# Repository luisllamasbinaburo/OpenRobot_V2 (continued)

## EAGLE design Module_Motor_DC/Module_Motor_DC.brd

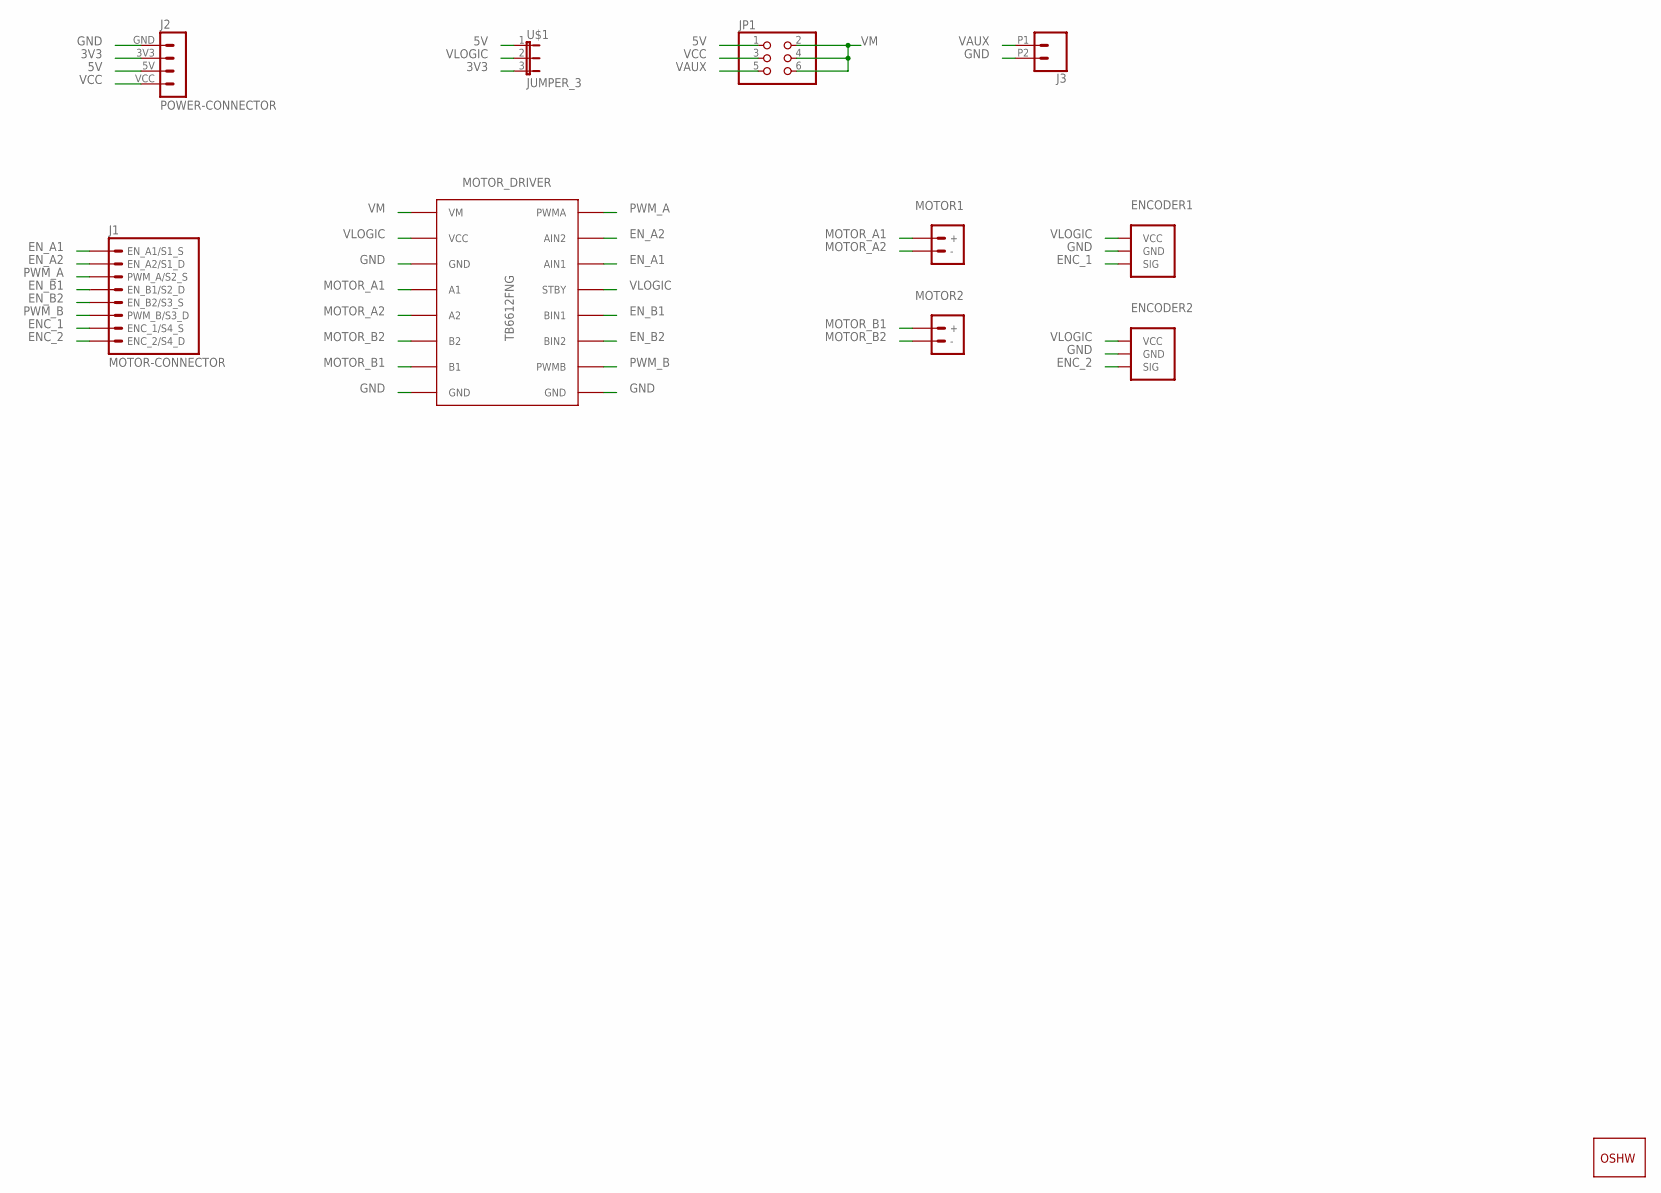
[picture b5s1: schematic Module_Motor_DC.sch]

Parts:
ENCODER1, ENCODER2: ENCODER/OCT; ENCODER
GOLD_ORB_SM1: OSHWLOGO_GOLD_ORB_MED; OSHW1
J1: MOTOR-CONNECTOR
J2: POWER-CONNECTOR
J3: CONN_022.54MM_SCREWTERM; 1X02_2.54_SCREWTERM
JP1: JUMPER_3X2/OCT; JUMPER_3X2
MOTOR1, MOTOR2: MOTOR-TERMINAL5MM; SCREWTERMINAL-5MM-2
MOTOR_DRIVER: TB6612FNG
U$1: JUMPER_3

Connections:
3V3: J2.3V3, U$1.3
5V: J2.5V, JP1.1, U$1.1
ENC_1: ENCODER1.SIG, J1.ENC_1/S4_S
ENC_2: ENCODER2.SIG, J1.ENC_2/S4_D
EN_A1: J1.EN_A1/S1_S, MOTOR_DRIVER.AIN1
EN_A2: J1.EN_A2/S1_D, MOTOR_DRIVER.AIN2
EN_B1: J1.EN_B1/S2_D, MOTOR_DRIVER.BIN1
EN_B2: J1.EN_B2/S3_S, MOTOR_DRIVER.BIN2
GND: ENCODER1.GND, ENCODER2.GND, J2.GND, J3.P2 (2), MOTOR_DRIVER.GND1 (GND), MOTOR_DRIVER.GND2 (GND), MOTOR_DRIVER.GND3 (GND)
MOTOR_A1: MOTOR1.+, MOTOR_DRIVER.A1
MOTOR_A2: MOTOR1.-, MOTOR_DRIVER.A2
MOTOR_B1: MOTOR2.+, MOTOR_DRIVER.B1
MOTOR_B2: MOTOR2.-, MOTOR_DRIVER.B2
PWM_A: J1.PWM_A/S2_S, MOTOR_DRIVER.PWMA
PWM_B: J1.PWM_B/S3_D, MOTOR_DRIVER.PWMB
VAUX: J3.P1 (1), JP1.5
VCC: J2.VCC, JP1.3
VLOGIC: ENCODER1.VCC, ENCODER2.VCC, MOTOR_DRIVER.STBY, MOTOR_DRIVER.VCC, U$1.2
VM: JP1.2, JP1.4, JP1.6, MOTOR_DRIVER.VM

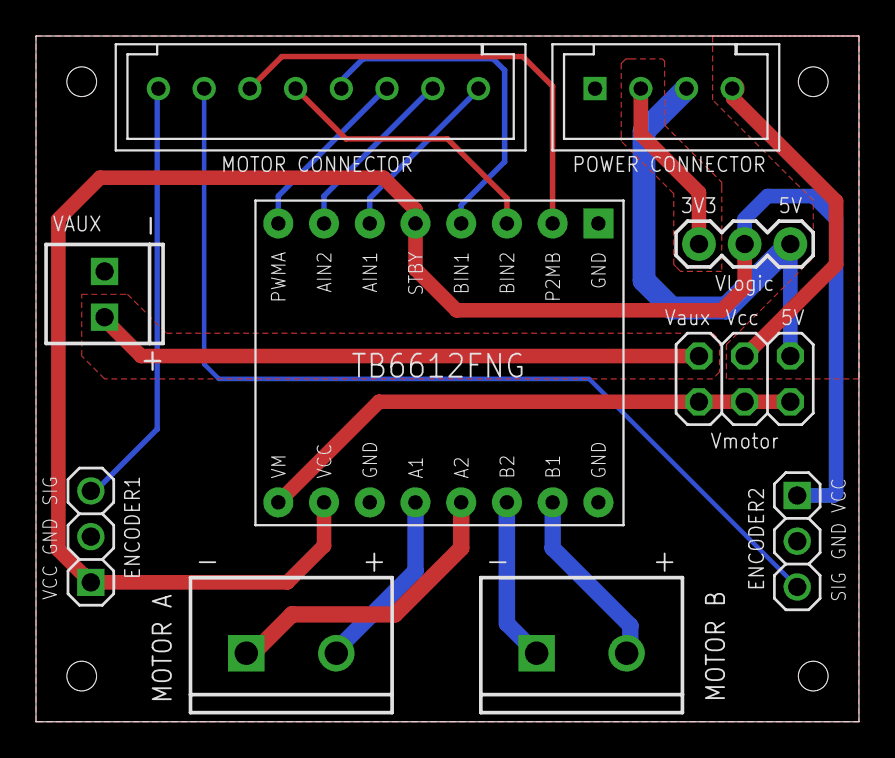
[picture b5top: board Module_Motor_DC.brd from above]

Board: 2 copper layers, 45.7 x 38.1 mm, 11 parts (1 on the bottom side), 19 nets.

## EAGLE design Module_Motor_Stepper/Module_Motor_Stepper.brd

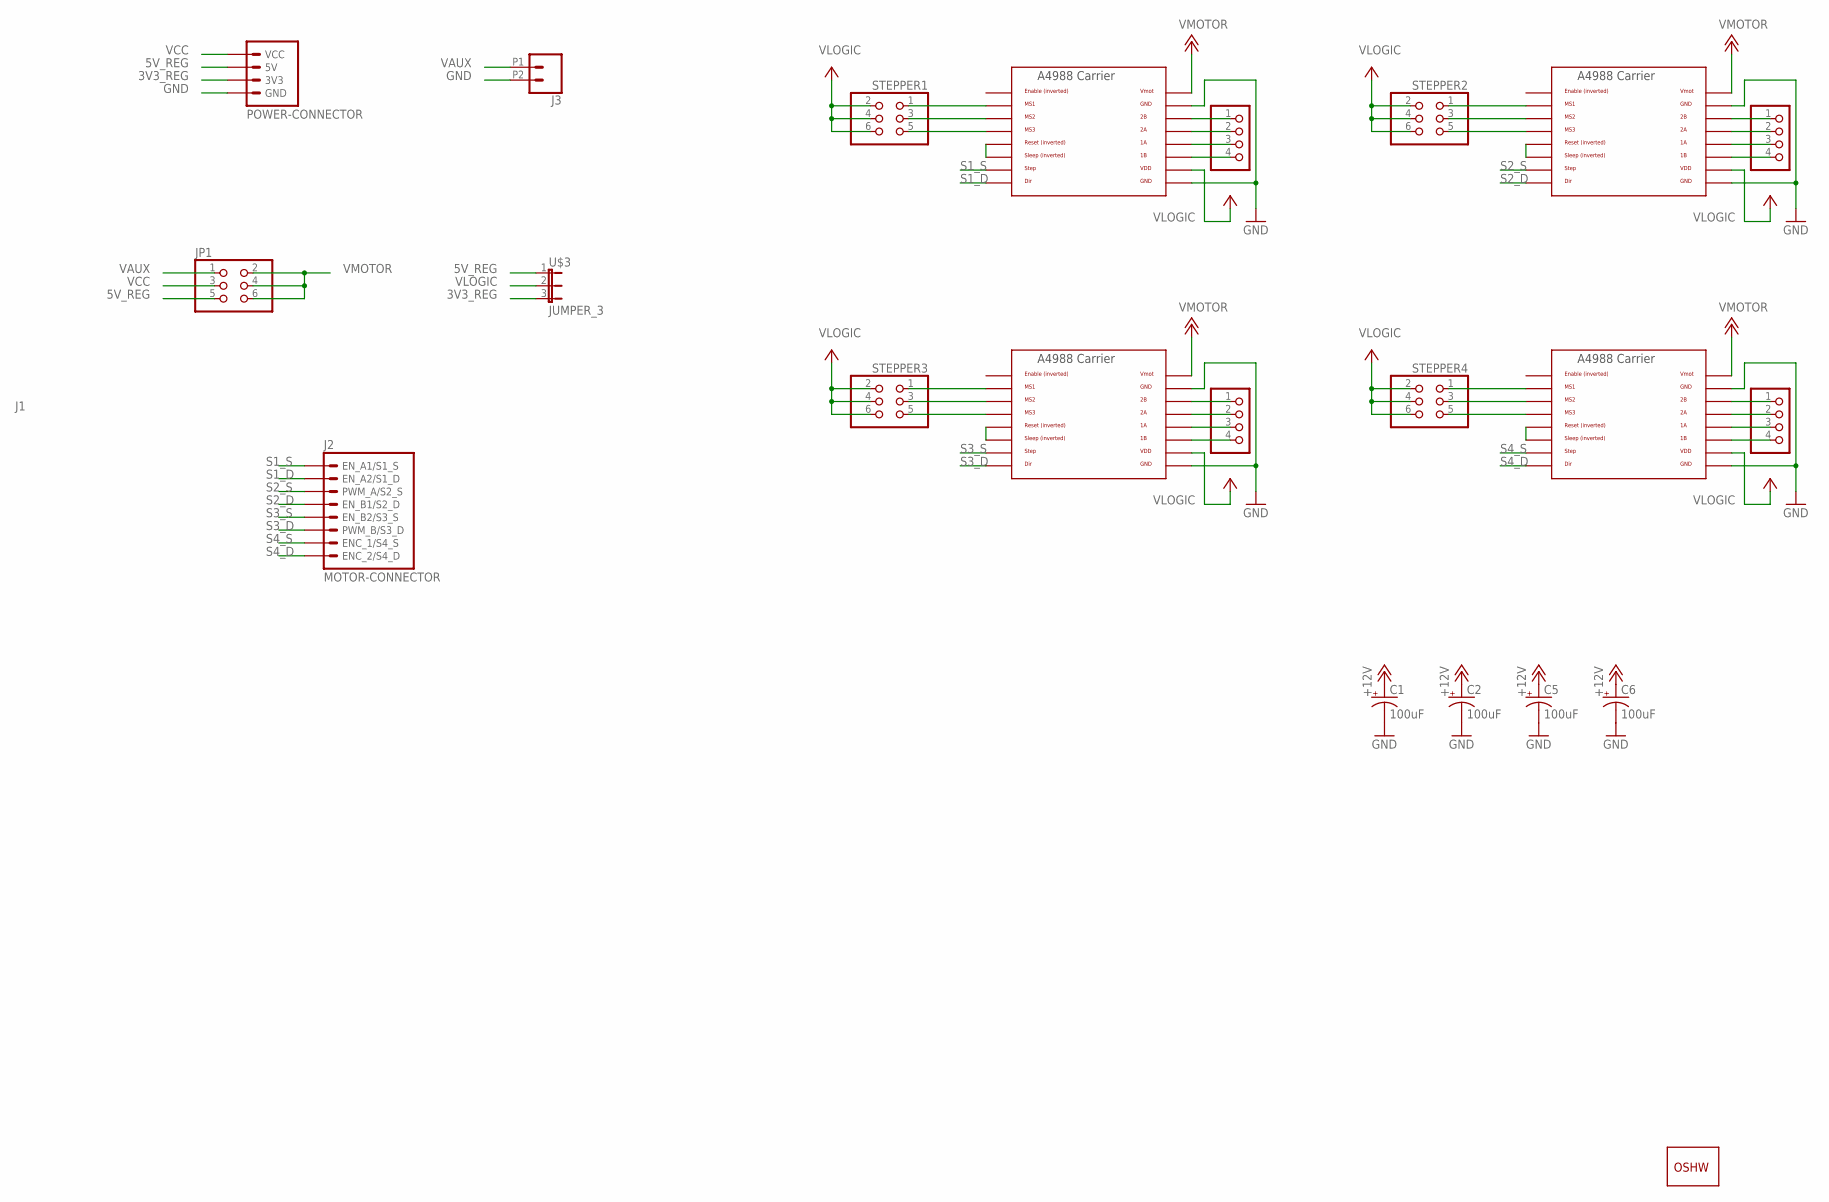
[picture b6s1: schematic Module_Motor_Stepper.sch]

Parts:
C1, C2, C5, C6: 100uF; 153CLV-0605
E0-MOT1, E0-MOT2, E0-MOT4, E0-MOT6: PINHD-1X4; 1X04
GOLD_ORB_SM1: OSHWLOGO_GOLD_ORB_MED; OSHW1
J1: POWER-CONNECTOR
J2: MOTOR-CONNECTOR
J3: CONN_022.54MM_SCREWTERM; 1X02_2.54_SCREWTERM
JP1: JUMPER_3X2/OCT; JUMPER_3X2
STEPPER1, STEPPER2, STEPPER3, STEPPER4: PINHD-2X3; 2X03
U$1, U$2, U$5, U$7: A4988BREAKOUT
U$3: JUMPER_3

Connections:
3V3_REG: J1.3V3, U$3.3
5V_REG: J1.5V, JP1.5, U$3.1
GND: C1.-, C2.-, C5.-, C6.-, J1.GND, J3.P2 (2), U$1.GND, U$1.GND@0 (GND), U$2.GND, U$2.GND@0 (GND), U$5.GND, U$5.GND@0 (GND), U$7.GND, U$7.GND@0 (GND)
unnamed: STEPPER1.5, U$1.MS3
unnamed: U$1.RST, U$1.SLP (SLEEP)
unnamed: STEPPER1.1, U$1.MS1
unnamed: STEPPER1.3, U$1.MS2
unnamed: E0-MOT1.1, U$1.2B
unnamed: E0-MOT1.2, U$1.2A
unnamed: E0-MOT1.3, U$1.1A
unnamed: E0-MOT1.4, U$1.1B
unnamed: STEPPER2.5, U$2.MS3
unnamed: U$2.RST, U$2.SLP (SLEEP)
unnamed: STEPPER2.1, U$2.MS1
unnamed: STEPPER2.3, U$2.MS2
unnamed: E0-MOT2.1, U$2.2B
unnamed: E0-MOT2.2, U$2.2A
unnamed: E0-MOT2.3, U$2.1A
unnamed: E0-MOT2.4, U$2.1B
unnamed: STEPPER3.5, U$5.MS3
unnamed: U$5.RST, U$5.SLP (SLEEP)
unnamed: STEPPER3.1, U$5.MS1
unnamed: STEPPER3.3, U$5.MS2
unnamed: E0-MOT4.1, U$5.2B
unnamed: E0-MOT4.2, U$5.2A
unnamed: E0-MOT4.3, U$5.1A
unnamed: E0-MOT4.4, U$5.1B
unnamed: STEPPER4.5, U$7.MS3
unnamed: U$7.RST, U$7.SLP (SLEEP)
unnamed: STEPPER4.1, U$7.MS1
unnamed: STEPPER4.3, U$7.MS2
unnamed: E0-MOT6.1, U$7.2B
unnamed: E0-MOT6.2, U$7.2A
unnamed: E0-MOT6.3, U$7.1A
unnamed: E0-MOT6.4, U$7.1B
S1_D: J2.EN_A2/S1_D, U$1.DIR
S1_S: J2.EN_A1/S1_S, U$1.STEP
S2_D: J2.EN_B1/S2_D, U$2.DIR
S2_S: J2.PWM_A/S2_S, U$2.STEP
S3_D: J2.PWM_B/S3_D, U$5.DIR
S3_S: J2.EN_B2/S3_S, U$5.STEP
S4_D: J2.ENC_2/S4_D, U$7.DIR
S4_S: J2.ENC_1/S4_S, U$7.STEP
VAUX: J3.P1 (1), JP1.1
VCC: J1.VCC, JP1.3
VLOGIC: STEPPER1.2, STEPPER1.4, STEPPER1.6, STEPPER2.2, STEPPER2.4, STEPPER2.6, STEPPER3.2, STEPPER3.4, STEPPER3.6, STEPPER4.2, STEPPER4.4, STEPPER4.6, U$1.VDD, U$2.VDD, U$3.2, U$5.VDD, U$7.VDD
VMOTOR: C1.+, C2.+, C5.+, C6.+, JP1.2, JP1.4, JP1.6, U$1.VMOT, U$2.VMOT, U$5.VMOT, U$7.VMOT

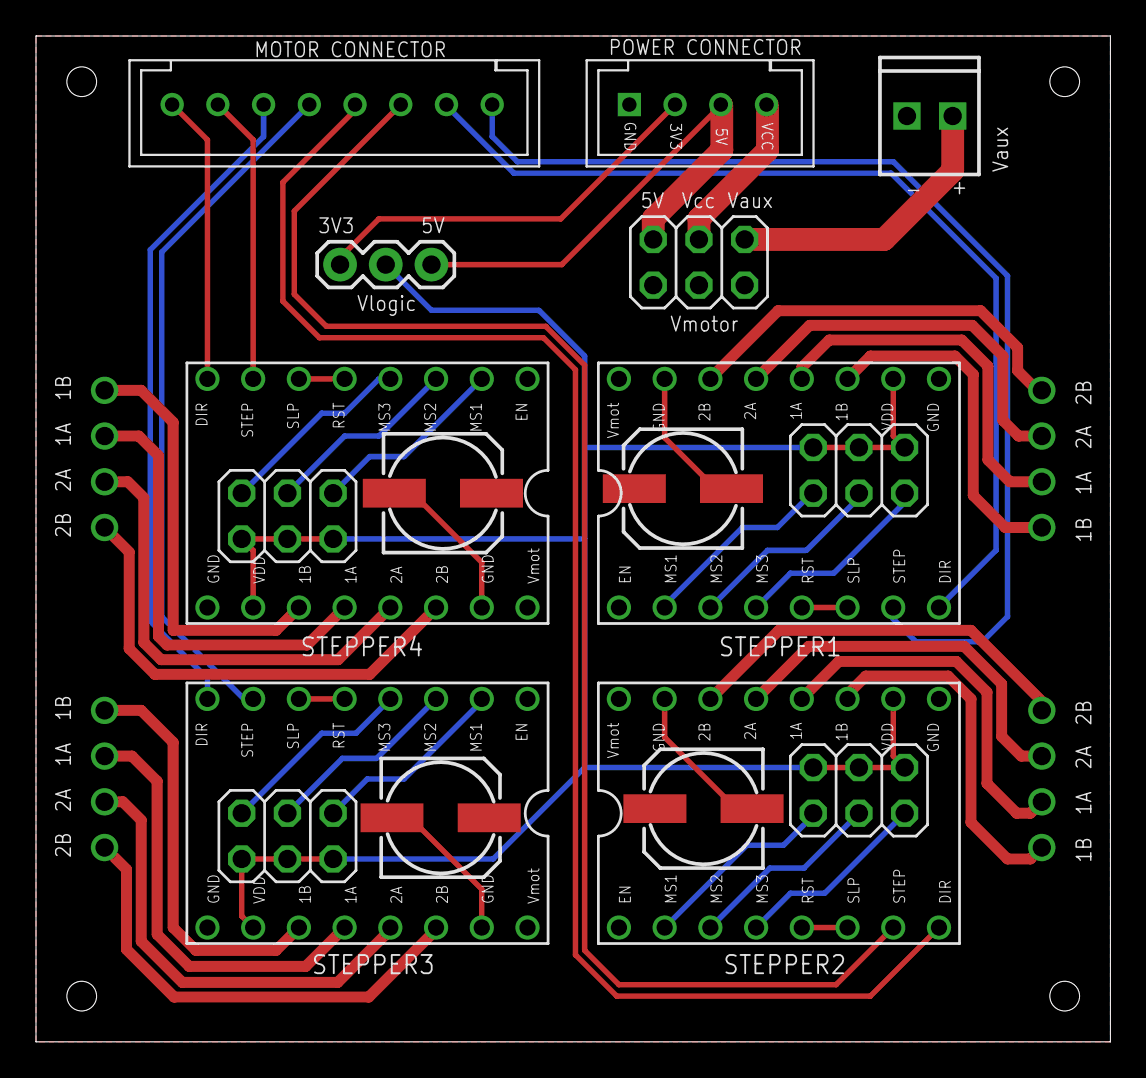
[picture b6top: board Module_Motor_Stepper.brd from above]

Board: 2 copper layers, 59.7 x 55.9 mm, 22 parts (1 on the bottom side), 47 nets.

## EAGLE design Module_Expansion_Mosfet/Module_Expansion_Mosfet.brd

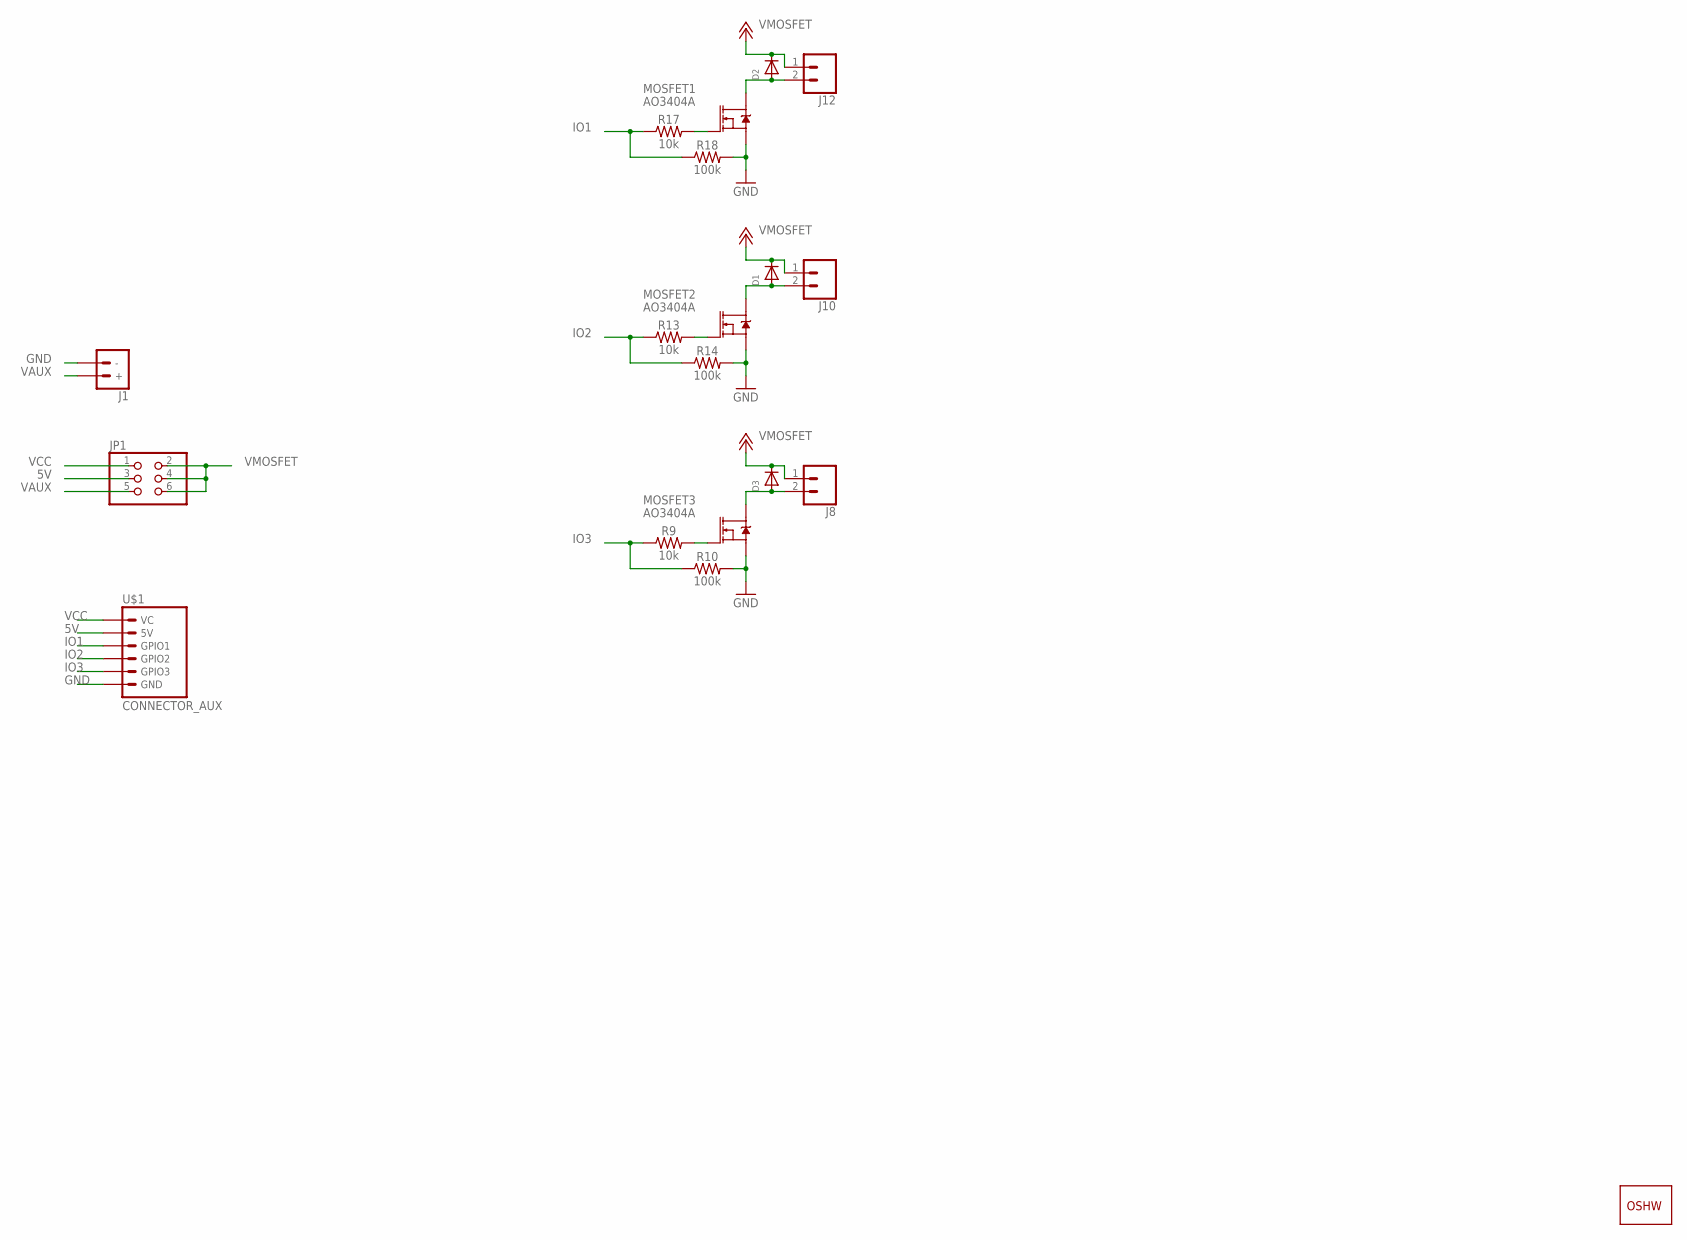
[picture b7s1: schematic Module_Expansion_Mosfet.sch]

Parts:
D1, D2, D3: DIODESOD-123; SOD-123
GOLD_ORB_SM1: OSHWLOGO_GOLD_ORB_MED; OSHW1
J1: POWER-TERMINAL2.54MM_SCREWTERM; 1X02_2.54_SCREWTERM
J8, J10, J12: CONN_02LOCK_LONGPADS; 1X02_LOCK_LONGPADS
JP1: JUMPER_3X2/OCT; JUMPER_3X2
MOSFET1, MOSFET2, MOSFET3: AO3404A; SOT23-3
R9, R13, R17: 10k; 1206
R10, R14, R18: 100k; 1206
U$1: CONNECTOR_AUX

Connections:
5V: JP1.3, U$1.5V
GND: J1.-, MOSFET1.2 (S), MOSFET2.2 (S), MOSFET3.2 (S), R10.2, R14.2, R18.2, U$1.GND
IO1: R17.1, R18.1, U$1.GPIO1
IO2: R13.1, R14.1, U$1.GPIO2
IO3: R9.1, R10.1, U$1.GPIO3
unnamed: MOSFET3.1 (G), R9.2
unnamed: D3.A, J8.2, MOSFET3.3 (D)
unnamed: MOSFET2.1 (G), R13.2
unnamed: D1.A, J10.2, MOSFET2.3 (D)
unnamed: MOSFET1.1 (G), R17.2
unnamed: D2.A, J12.2, MOSFET1.3 (D)
VAUX: J1.+, JP1.5
VCC: JP1.1, U$1.VC
VMOSFET: D1.C, D2.C, D3.C, J8.1, J10.1, J12.1, JP1.2, JP1.4, JP1.6

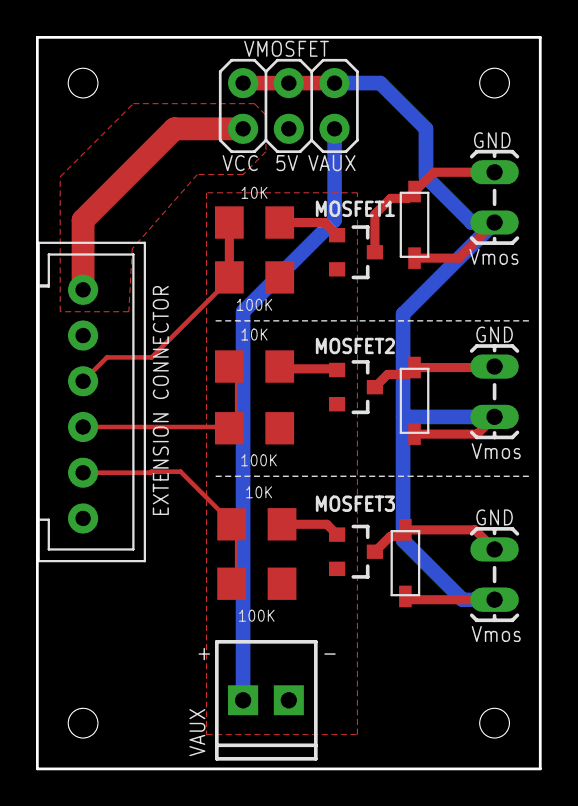
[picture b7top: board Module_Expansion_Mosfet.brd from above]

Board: 2 copper layers, 27.9 x 40.6 mm, 19 parts (1 on the bottom side), 14 nets.

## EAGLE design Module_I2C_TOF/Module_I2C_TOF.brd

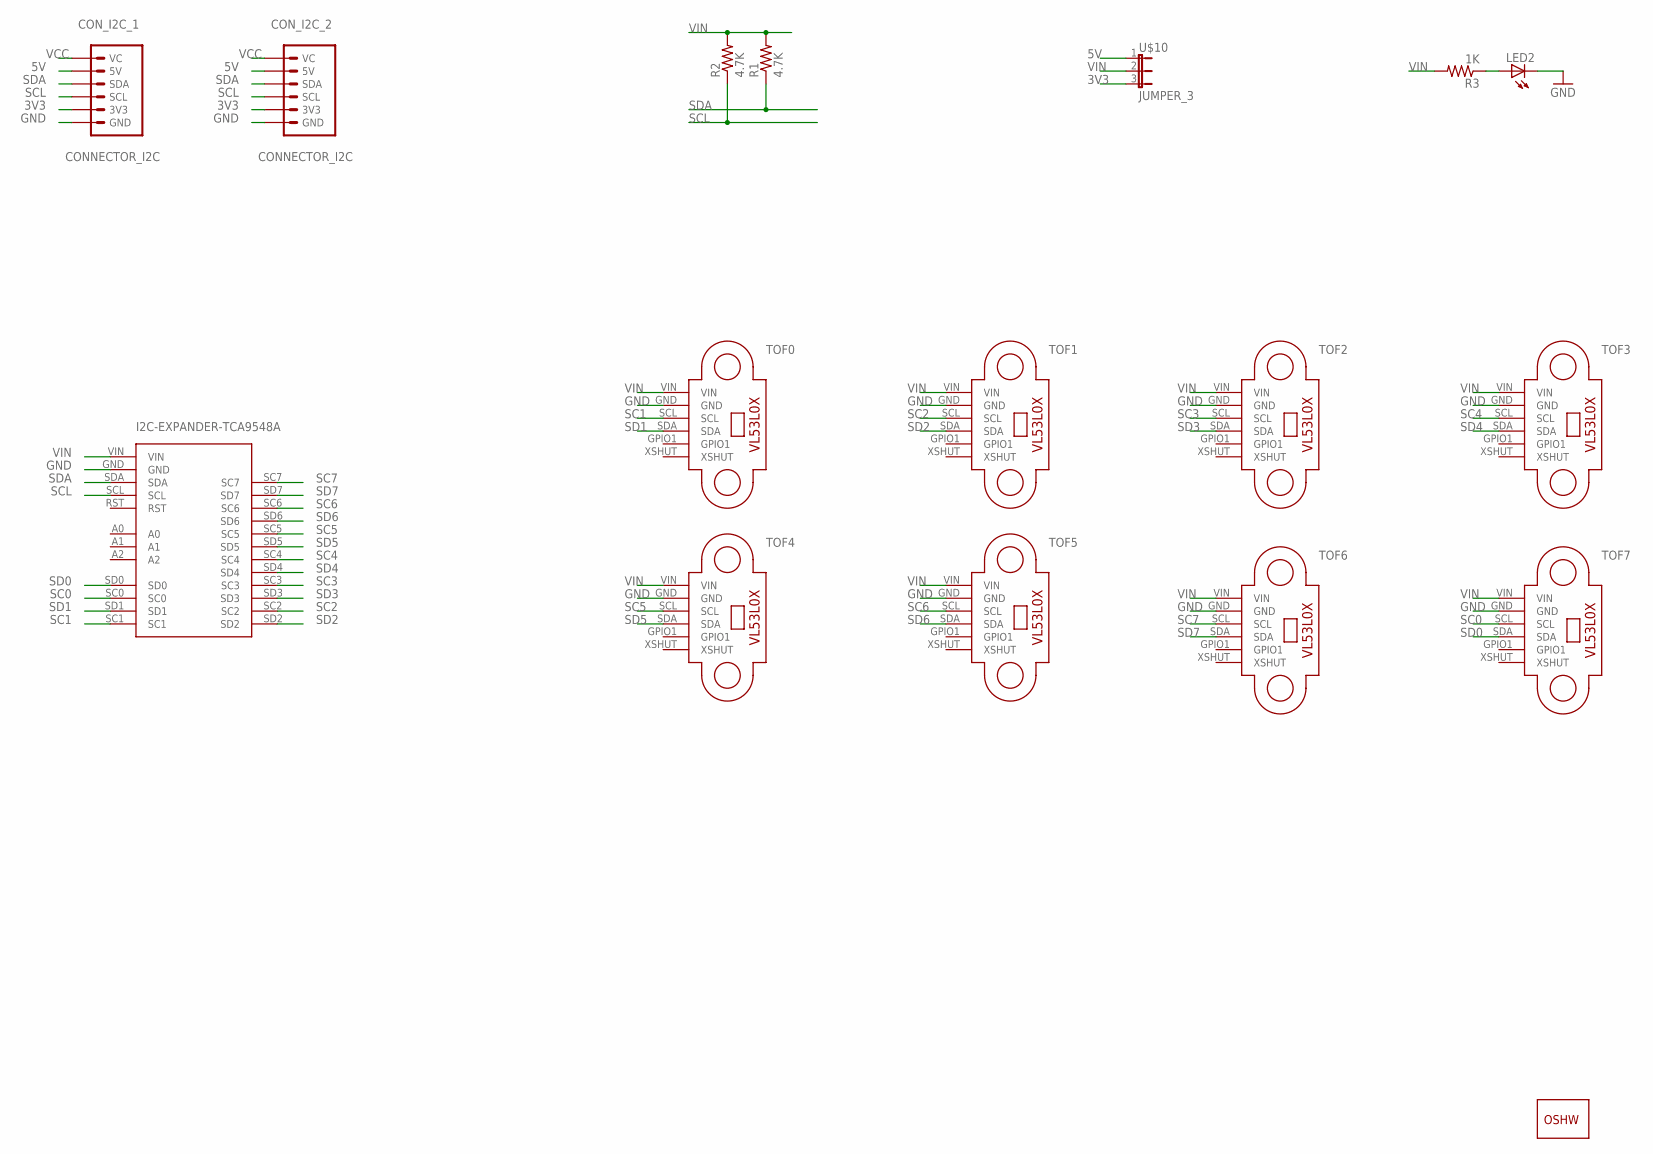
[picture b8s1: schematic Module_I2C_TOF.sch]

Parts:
CON_I2C_1, CON_I2C_2: CONNECTOR_I2C
GOLD_ORB_SM1: OSHWLOGO_GOLD_ORB_MED; OSHW1
LED2: LEDCHIP-LED0805; CHIP-LED0805
R1, R2: 4.7K; R0805
R3: 1K; R0805
TOF0, TOF1, TOF2, TOF3, TOF4, TOF5, TOF6, TOF7: RANGING-SENSOR-VL53L0X
U$9: I2C-EXPANDER-TCA9548A
U$10: JUMPER_3

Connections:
3V3: CON_I2C_1.3V3, CON_I2C_2.3V3, U$10.3
5V: CON_I2C_1.5V, CON_I2C_2.5V, U$10.1
GND: CON_I2C_1.GND, CON_I2C_2.GND, LED2.C, TOF0.GND, TOF1.GND, TOF2.GND, TOF3.GND, TOF4.GND, TOF5.GND, TOF6.GND, TOF7.GND, U$9.GND
unnamed: LED2.A, R3.1
SC0: TOF7.SCL, U$9.SC0
SC1: TOF0.SCL, U$9.SC1
SC2: TOF1.SCL, U$9.SC2
SC3: TOF2.SCL, U$9.SC3
SC4: TOF3.SCL, U$9.SC4
SC5: TOF4.SCL, U$9.SC5
SC6: TOF5.SCL, U$9.SC6
SC7: TOF6.SCL, U$9.SC7
SCL: CON_I2C_1.SCL, CON_I2C_2.SCL, R2.1, U$9.SCL
SD0: TOF7.SDA, U$9.SD0
SD1: TOF0.SDA, U$9.SD1
SD2: TOF1.SDA, U$9.SD2
SD3: TOF2.SDA, U$9.SD3
SD4: TOF3.SDA, U$9.SD4
SD5: TOF4.SDA, U$9.SD5
SD6: TOF5.SDA, U$9.SD6
SD7: TOF6.SDA, U$9.SD7
SDA: CON_I2C_1.SDA, CON_I2C_2.SDA, R1.1, U$9.SDA
VCC: CON_I2C_1.VC, CON_I2C_2.VC
VIN: R1.2, R2.2, R3.2, TOF0.VIN, TOF1.VIN, TOF2.VIN, TOF3.VIN, TOF4.VIN, TOF5.VIN, TOF6.VIN, TOF7.VIN, U$9.VIN, U$10.2

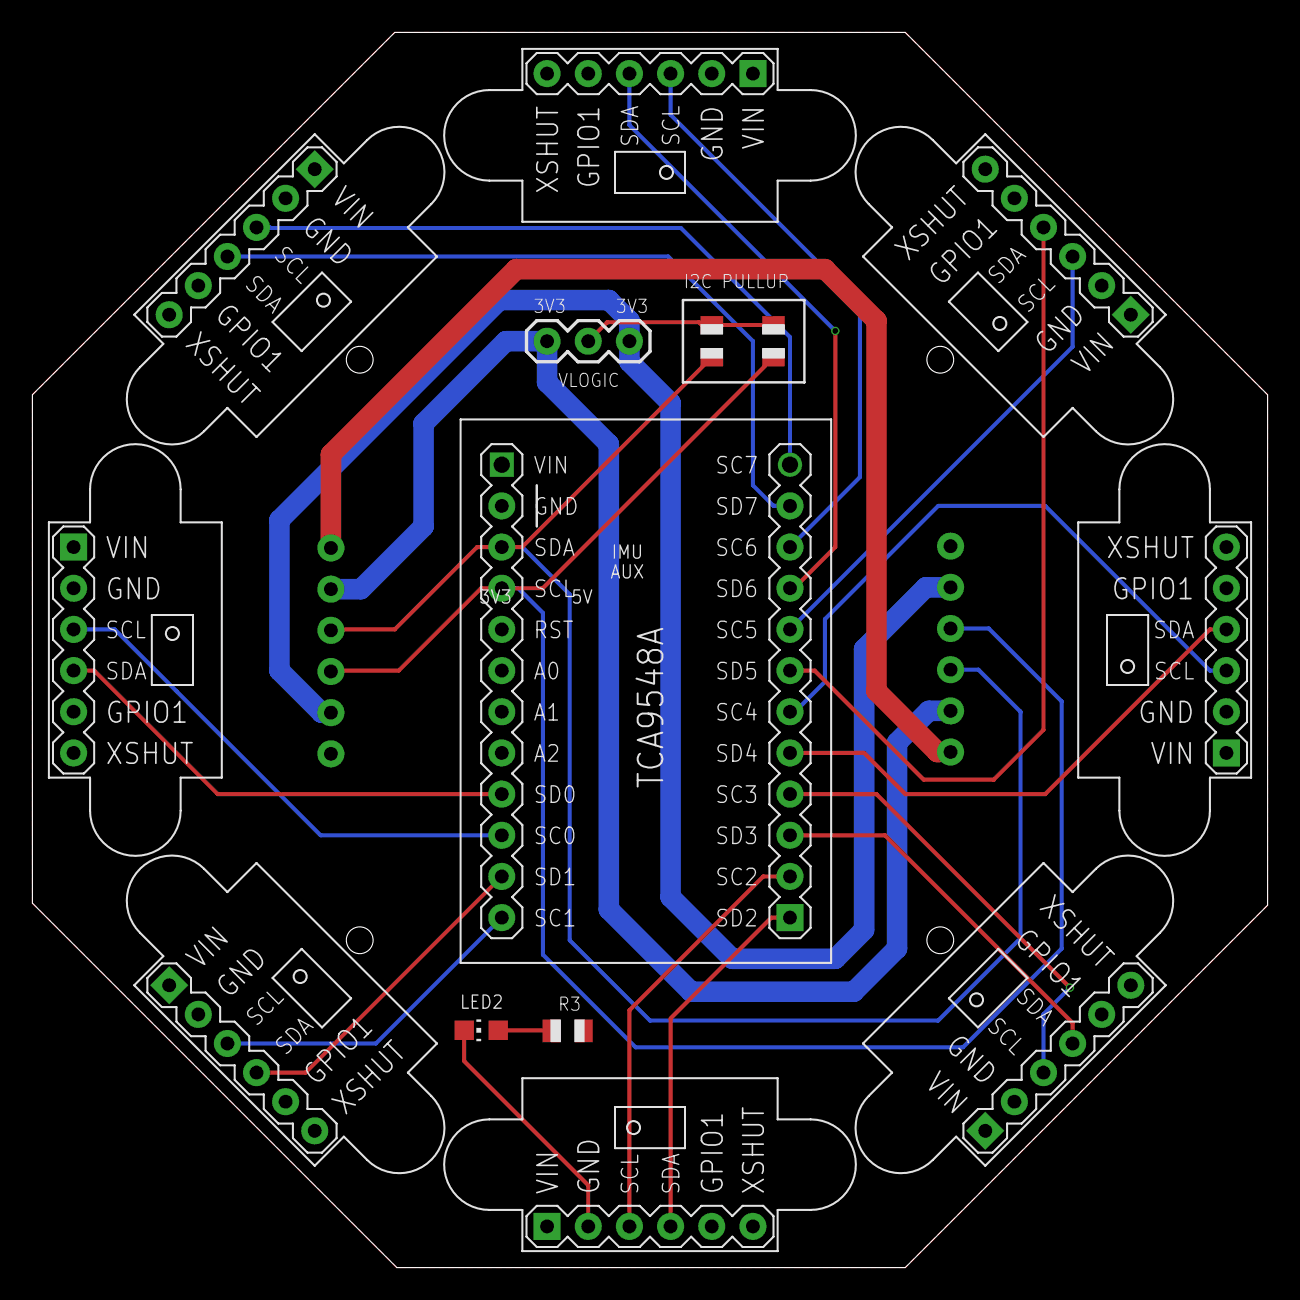
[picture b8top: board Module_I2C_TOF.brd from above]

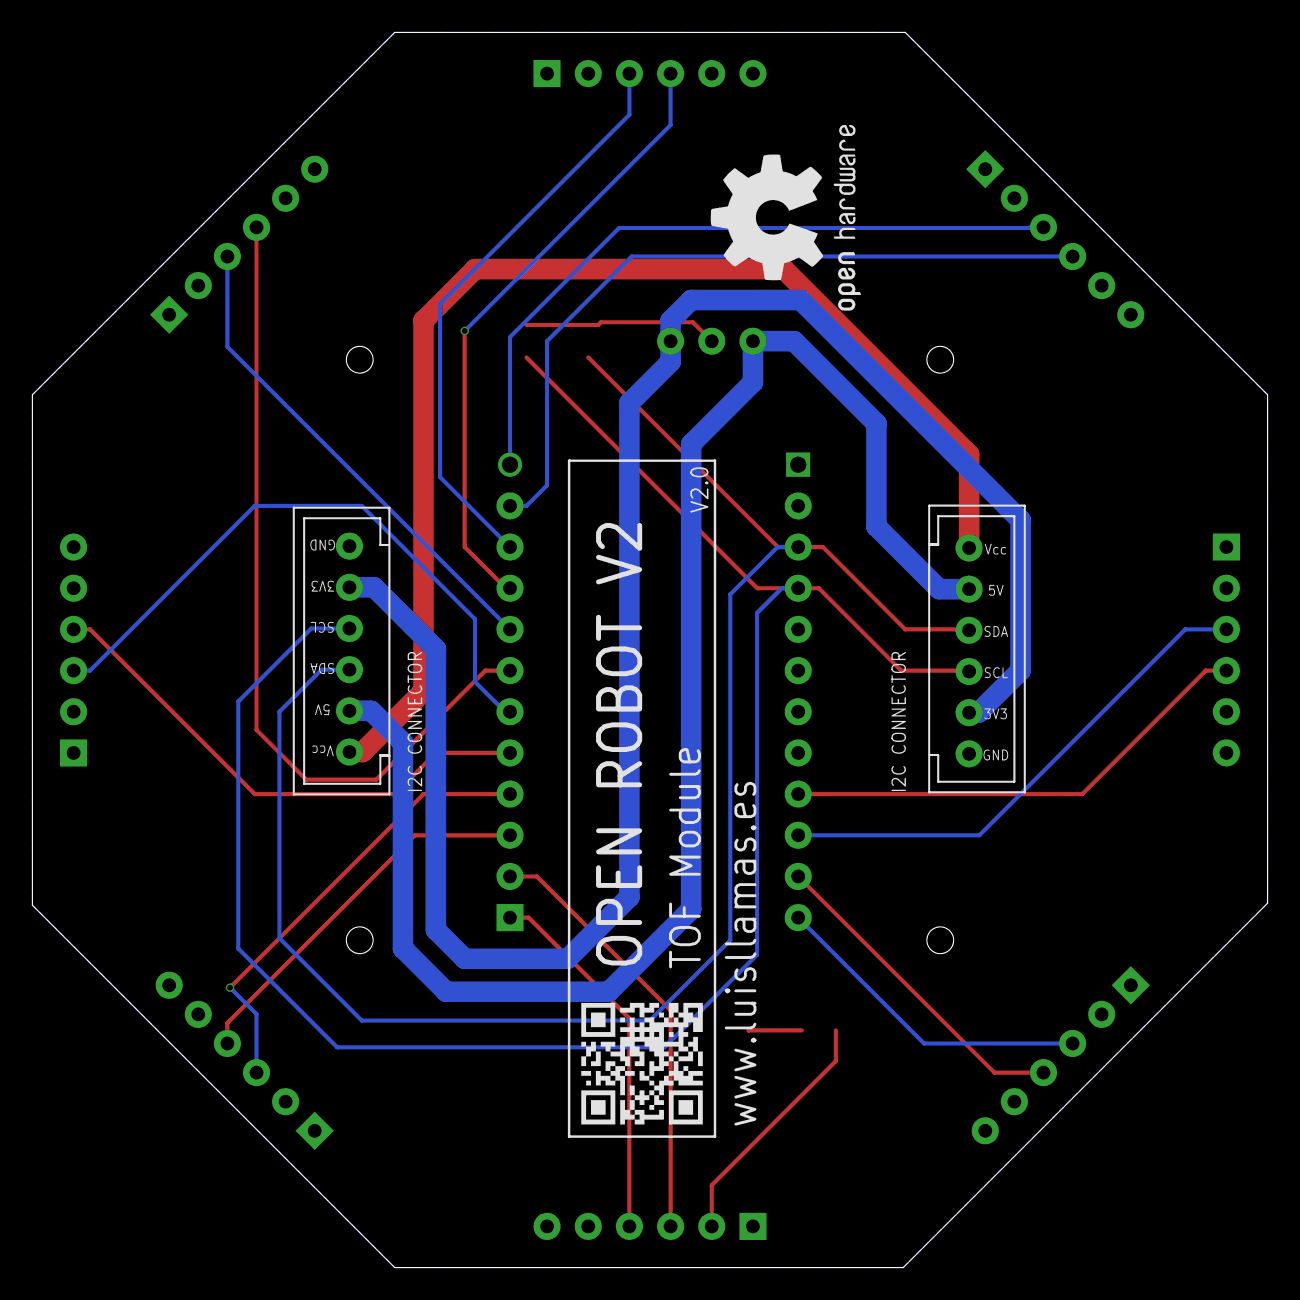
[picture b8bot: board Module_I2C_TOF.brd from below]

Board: 2 copper layers, 76.2 x 76.2 mm, 17 parts (3 on the bottom side), 24 nets.

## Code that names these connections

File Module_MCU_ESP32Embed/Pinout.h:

#pragma once

static const uint8_t UART_TX = 1;
static const uint8_t UART_RX = 3;

static const uint8_t IR1 = 2;
static const uint8_t TOUCH2 = 2;

static const uint8_t SERVO6 = 5;

static const uint8_t TOUCH5 = 12;

static const uint8_t MOTOR1_A = 23;
static const uint8_t STEPPER1_STEP = 23;

static const uint8_t MOTOR1_B = 19;
static const uint8_t STEPPER1_DIR = 19;

static const uint8_t MOTOR1_PWM = 27;
static const uint8_t STEPPER2_STEP = 27;

static const uint8_t MOTOR2_A = 18;
static const uint8_t STEPPER2_DIR = 18;

static const uint8_t MOTOR2_B = 4;
static const uint8_t STEPPER3_STEP = 4;

static const uint8_t MOTOR2_PWM = 13;
static const uint8_t STEPPER3_DIR = 13;

static const uint8_t ENCODER1 = 32;
static const uint8_t STEPPER4_STEP = 32;

static const uint8_t ENCODER2 = 33;
static const uint8_t STEPPER4_DIR = 33;


static const uint8_t SERVO3 = 14;
static const uint8_t TOUCH7 = 14;

static const uint8_t IR_2 = 15;
static const uint8_t TOUCH3 = 15;

static const uint8_t AUX3 = 16;
static const uint8_t SERVO5 = 16;
static const uint8_t SONAR3 = 16;
static const uint8_t UART2_TX = 16;

static const uint8_t SONAR2 = 17;
static const uint8_t SERVO4 = 17;
static const uint8_t UART2_RX = 17;


static const uint8_t I2C_SDA = 21;
static const uint8_t I2C_SCL = 22;

static const uint8_t AUX1 = 25;
static const uint8_t DAC_1 = 25;
static const uint8_t SERVO1 = 25;
static const uint8_t SONAR1 = 25;

static const uint8_t AUX2 = 26;
static const uint8_t DAC_2 = 26;
static const uint8_t SERVO2 = 26;

static const uint8_t ANALOG3 = 34;
static const uint8_t IR3 = 34;

static const uint8_t BAT_SENSE = 35;

static const uint8_t ANALOG1 = 36;
static const uint8_t IR4 = 36;

static const uint8_t ANALOG2 = 39;
static const uint8_t IR5 = 39;

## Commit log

2021-05-20 Added image
2021-05-20 Rename image
2021-06-02 Change I2C pull-ups, update silkscreen
